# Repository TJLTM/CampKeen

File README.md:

# CampKeen
An OpenSource RV monitoring hardware project. Currently i'm targeting my setup but leaving enough to adapt to other systems. This will allow a central place to monitor all of the various things in an RV and will be able to be integrated with an external system like Home assistant (when I get to that it will have a separate Repo for the component) or custom setups. As well control some things around the RV. Like in this case, i have small holding tanks and to keep them from overflowing i have added water pump and city (external water hook up control) in both the bathroom and in the kitchen. This does not have a wifi or Ethernet capability. This is RS232 or USB (via the MEGA2560) device only. 

What this can monitor: 
1. Holding Tanks - Grey/Sewage via galvanic sensors (posts in the tank) these are the ones i'm using (https://www.amazon.com/gp/product/B07YVK2V2K/ref=ppx_yo_dt_b_search_asin_title?ie=UTF8&psc=1 and https://www.amazon.com/gp/product/B07SVDTHHG/ref=ppx_yo_dt_b_search_asin_title?ie=UTF8&psc=1)
2. Fresh water tank - Resistance (https://www.amazon.com/gp/product/B00Y831WPM/ref=ppx_yo_dt_b_asin_title_o07_s01?ie=UTF8&th=1&psc=1)
3. Camper Battery Voltage
4. Power/Energy Monitoring (https://github.com/CircuitSetup/Split-Single-Phase-Energy-Meter)
5. Tempetures around the RV especially and Fridge and Freezer (https://www.amazon.com/gp/product/B087NMHGX8/ref=ppx_yo_dt_b_asin_title_o07_s01?ie=UTF8&psc=1)
6. Generator Fuel Pressure (https://www.amazon.com/gp/product/B07N8SX347/ref=ppx_yo_dt_b_search_asin_title?ie=UTF8&th=1 be careful of these they may or may not be DOA or last only a few weeks depending i haven't found a good source that isn't a crap shoot) 
7. LPG tank level - No link as this is the original tank and sensor that came with the 1978 Pace Arrow it's resistance based but single wire it is similar to https://parts.unitedrv.com/products/remote-ohm-sender-lp-gas-tank-90-degree?currency=USD&variant=36385562881&_vsrefdom=adwords&msclkid=ae7c158e8c431c0739b97415690580d9&utm_source=bing&utm_medium=cpc&utm_campaign=**LP%20Shopping%20-%20Catch%20All&utm_term=4583245501779595&utm_content=Catch%20All

What this can control:
1. WaterPump
2. City Water Valve (https://www.amazon.com/gp/product/B07N6246YB/ref=ppx_yo_dt_b_asin_title_o05_s00?ie=UTF8&th=1)
I do this with push buttons (two one in the kitchen and one in the bathroom for my set up) with LEDs to let you know that the water is on. Be it the City Water or Tank Via the pump. 
i have also included a timer. that can be set for how long you would ike the water to remain on when either button is pressed.

Other Stuff
1. There are 6 spare outputs that can be used to control whatever you want 
2. Same goes for 6 spare inputs 
3. I2C output for an 20x4 LCD to display current status (https://www.amazon.com/gp/product/B07MTFDHXZ/ref=ppx_yo_dt_b_search_asin_title?ie=UTF8&psc=1)
4. Siren to alert when the tanks are full
5. Warning LED (This and the siren can be programmed for other items for warnings) 
6. 2 Spare Buffered ADCs with POTs 

Some Specs and Installation Notes: 
1. I designed this for 12Vdc systems only so i'm not sure if it would work on a 24Vdc system might. might not. 
2. The Inputs are buffered and you can just supply 12Vdc in as a logical 'On' 
3. Outputs, Although technically you could power the waterpump directly off of the unit. this is not recommended. nor encouraged in any way, shape or form. These outputs are used to trigger remove 12Vdc relays like the following: https://www.summitracing.com/parts/pco-5591pt

currently working on https://github.com/TJLTM/CampKeen-HomeAssistant-Custom-Integration this may roll into a true python package later on to handle communication 

FUTURE: 
Better docs with installation pictures for my setup.

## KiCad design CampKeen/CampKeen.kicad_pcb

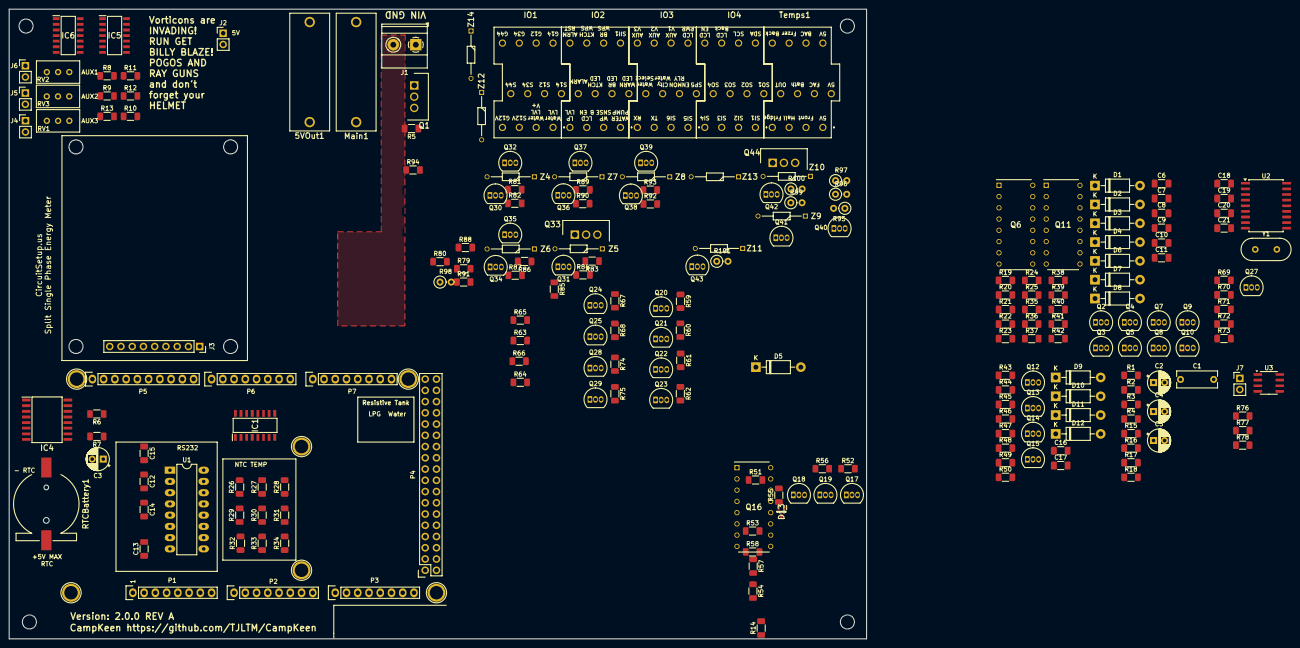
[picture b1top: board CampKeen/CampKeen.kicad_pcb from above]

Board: 4 copper layers, 193.7 x 142.2 mm, 228 parts (0 on the bottom side), 176 nets, no tracks yet.

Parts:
5VOut1: VS; BK_HTC-15M
C1: 0.1uF; C_Rect_L9.0mm_W3.6mm_P7.50mm_MKT
C2, C3, C4, C5: 1uF; CP_Radial_D5.0mm_P2.50mm
C6, C7, C8, C9, C10, C11, C12, C13, C14, C15, C16, C17: 22nF; C_1206_3216Metric_Pad1.33x1.80mm_HandSolder
C18, C19: 22pf; C_1206_3216Metric_Pad1.33x1.80mm_HandSolder
C20, C21: 100nf; C_1206_3216Metric_Pad1.33x1.80mm_HandSolder
D1, D2, D3, D4, D5, D6, D7, D8, D9, D10, D11, D12: 1N4007; D_DO-41_SOD81_P10.16mm_Horizontal
D13: PESD5V0L2UU,115; SOT65P210X110-3N
IC1: CD74HC4050ME4; SOIC127P600X175-16N
IC4: DS3231SN#; SOIC127P1032X265-16N
IC5, IC6: SN7404DR; SOIC127P600X175-14N
IO1: IO1; 1727751
IO2: IO2; 1727751
IO3: IO3; 1727751
IO4: IO4; 1727751
J1: Vin; TerminalBlock_Phoenix_MKDS-1,5-2-5.08_1x02_P5.08mm_Horizont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
J2, J4, J5, J6, J7: Conn_01x02; PinHeader_1x02_P2.54mm_Vertical
J3: CircuitSetupsSplitPhase; PinSocket_1x09_P2.54mm_Vertical
Main1: VS; BK_HTC-15M
P1: Power; Socket_Strip_Arduino_1x08
P2, P3: Analog; Socket_Strip_Arduino_1x08
P4: Digital; Socket_Strip_Arduino_2x18
P5: PWM; Socket_Strip_Arduino_1x10
P6: PWM; Socket_Strip_Arduino_1x08
P7: Communication; Socket_Strip_Arduino_1x08
P8, P9, P10, P11, P12, P13: CONN_01X01; Arduino_1pin
Q1, Q33, Q44: IRF9Z34NPBF; TO254P469X1042X1967-3P
Q2, Q3, Q4, Q5, Q7, Q8, Q9, Q10, Q12, Q13, Q14, Q15, Q17, Q18, Q19, Q20, Q21, Q22, Q23, Q24, Q25, Q27, Q28, Q29, Q30, Q31, Q32, Q34, Q35, Q36, Q37, Q38, Q39, Q40, Q41, Q42, Q43: 2N7000; TO-92_Inline
Q6, Q11, Q16: LTV-847; DIP762W60P254L1984H450Q16N
R1, R57, R59, R63, R65, R68, R71, R74, R78, R80, R83, R86, R89, R92: 100k; R_1206_3216Metric_Pad1.30x1.75mm_HandSolder
R2, R3, R10, R11, R12, R13, R14, R15, R16, R17, R18, R58, R60, R64, R66, R69, R72, R75, R79, R81, R84, R87, R90, R93, R94: 10k; R_1206_3216Metric_Pad1.30x1.75mm_HandSolder
R4, R6, R7, R8, R9: 47K; R_1206_3216Metric_Pad1.30x1.75mm_HandSolder
R5: 19.2K; R_1206_3216Metric_Pad1.30x1.75mm_HandSolder
R19, R20, R21, R22, R27, R28, R30, R32, R43, R44, R45, R46, R55, R56, R61, R62, R67, R70, R73, R76, R77, R82, R85, R88, R91: 1M; R_1206_3216Metric_Pad1.30x1.75mm_HandSolder
R23, R25, R26, R35, R37, R38, R47, R48, R49, R50: 330; R_1206_3216Metric_Pad1.30x1.75mm_HandSolder
R24, R36: 300; R_1206_3216Metric_Pad1.30x1.75mm_HandSolder
R29, R31, R33, R34, R39, R40, R41, R42, R51, R52, R53, R54: 22k; R_1206_3216Metric_Pad1.30x1.75mm_HandSolder
R95: 17k; R_Axial_DIN0207_L6.3mm_D2.5mm_P2.54mm_Vertical
R96: 120; R_Axial_DIN0207_L6.3mm_D2.5mm_P2.54mm_Vertical
R97: 1M; R_Axial_DIN0207_L6.3mm_D2.5mm_P2.54mm_Vertical
R98: 100k; R_Axial_DIN0207_L6.3mm_D2.5mm_P2.54mm_Vertical
R99: 10k; R_Axial_DIN0207_L6.3mm_D2.5mm_P2.54mm_Vertical
R100, R101: 47; R_Axial_DIN0207_L6.3mm_D2.5mm_P2.54mm_Vertical
RTCBattery1: S8411-45R; S8411-45R_1
RV1, RV2, RV3: 500k; Potentiometer_Bourns_3296W_Vertical
Temps1: Temps; 1727751
U1: MAX232; DIP-16_W7.62mm_LongPads
U2: MCP2515-xSO; SOIC-18W_7.5x11.6mm_P1.27mm
U3: MCP2551-I-SN; SOIC-8_3.9x4.9mm_P1.27mm
Y1: 16MHz; Crystal_HC49-U_Vertical
Z4, Z5, Z6, Z7, Z8, Z9, Z10, Z11, Z12, Z13, Z14: BZX79C10; DIOAD1068W53L380D172

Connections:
+3V3: IC1.1 (VCC), P1.4
+5P: C1.1, IC4.2 (VCC), P1.5, P4.35, P4.36
+5V: 5VOut1.2, C5.2, C20.1, C21.1, IC5.14 (VCC), IC6.14 (VCC), J2.1, R2.1, R3.1, R23.1, R24.1, R25.1, R26.1, R29.1, R31.1, R33.1, R34.1, R35.1, R36.1, R37.1, R38.1, R39.1, R40.1, R41.1, R42.1, R47.1, R48.1, R49.1, R50.1, R51.1, R52.1, R53.1, R54.1, R94.2, Temps1.1, Temps1.2, Temps1.3, U1.16 (VCC), U2.18 (VDD), U3.3 (VDD)
+12V: Q1.3, Q33.3, R4.2, R57.1, R59.1, R63.1, R65.1, R68.1, R71.1, R74.1, R78.1, R80.1, R83.1, R86.1, R89.1, R92.1, Z4.1, Z5.1, Z6.1, Z7.1, Z8.1, Z9.1, Z10.1, Z11.1, Z12.1, Z13.1
+BATT: J1.1, Main1.1
/3.3CS: IC1.15 (6Y), J3.6
/3.3MISO: IC1.5 (2A), J3.4
/3.3MOSI: IC1.6 (3Y), J3.3
/3.3SCLK: IC1.2 (1Y), J3.5
/CANBUS-MCP2515/RXtoCANTC: U2.2 (RXCAN), U3.4 (RXD)
/CANBUS-MCP2515/TXtoCANTC: U2.1 (TXCAN), U3.1 (TXD)
/Inputs with interrupts/AlarmResetTTL: IC5.1 (1A), Q16.16 (COLLECTOR_4), R51.2
/Inputs with interrupts/BathroomTTL: IC5.5 (3A), Q16.12 (COLLECTOR_2), R53.2
/Inputs with interrupts/KitchenTTL: IC5.3 (2A), Q16.10 (COLLECTOR_1), R54.2
/Inputs with interrupts/ShowerInTTL: IC5.13 (6A), Q16.14 (COLLECTOR_3), R52.2
/Inputs/EnableLCDIn: C7.1, Q3.2 (G), R20.1
/Inputs/EnableLCDTTL: Q6.14 (COLLECTOR_3), R33.2
/Inputs/LCDBackLIGHTIn: C8.1, Q4.2 (G), R21.1
/Inputs/LCDBackLIGHTTTL: Q6.12 (COLLECTOR_2), R31.2
/Inputs/SP1TTL: IC6.5 (3A), Q11.16 (COLLECTOR_4), R42.2
/Inputs/SP2TTL: IC6.13 (6A), Q11.14 (COLLECTOR_3), R41.2
/Inputs/SP3TTL: IC6.11 (5A), Q11.12 (COLLECTOR_2), R40.2
/Inputs/SP4TTL: IC6.9 (4A), Q11.10 (COLLECTOR_1), R39.2
/Inputs/WaterPumpSenseTTL: IC5.11 (5A), Q6.16 (COLLECTOR_4), R34.2
/Inputs/WaterSourceTTL: IC6.3 (2A), Q6.10 (COLLECTOR_1), R29.2
A0: P2.1, R6.2
A1: IO2.10, P2.2, R100.1
A2: IO1.1, P2.3, R101.2
A3: P2.4, R11.2, Temps1.5
A4: P2.5, R12.2, Temps1.6
A5: P2.6, R18.2, Temps1.7
A6: P2.7, R17.2, Temps1.8
A7: P2.8, R16.2, Temps1.9
A8: P3.1, R15.2, Temps1.10
A9: P3.2, R14.2, Temps1.11
A10: P3.3, R13.2, Temps1.12
A11: P3.4, R10.2, Temps1.4
A12: P3.5, R8.2
A13: P3.6, R9.2
A14: IC4.14 (VBAT), P3.7, RTCBattery1.1 (+)
A15: P3.8, R7.2
AUXVoltage0: IO3.6, RV2.1
AUXVoltage1: IO3.9, RV3.1
AUXVoltage2: IO3.12, RV1.1
AlarmTTL: IC5.2 (1Y), P6.5
BRLED: P6.1, Q18.2 (G), R56.1
BathRoomTTL: IC5.6 (3Y), P4.16
CAN1CS: P4.30, U2.16 (~CS)
CLK: IC1.3 (1A), P4.3, U2.13 (SCK)
COMRX5to33TTL: IC1.12 (5Y), P7.6
COMRXTTL: P7.4, U1.12 (R1OUT)
COMTX5to33TTL: IC1.9 (4A), P7.5
COMTXTTL: P7.3, U1.11 (T1IN)
CWV: P4.27, Q29.2 (G), Q40.2 (G), R73.1
EnCS: IC1.14 (6A), P4.31
GND: C1.2, C3.1, C6.2, C7.2, C8.2, C9.2, C10.2, C11.2, C12.2, C13.2, C14.2, C15.2, C16.2, C17.2, C18.2, C19.2, C20.2, C21.2, D13.3 (COMMON_ANODE), IC1.8 (GND), IC4.5 (N.C._1), IC4.6 (N.C._2), IC4.7 (N.C._3), IC4.8 (N.C._4), IC4.9 (N.C._5), IC4.10 (N.C._6), IC4.11 (N.C._7), IC4.12 (N.C._8), IC4.13 (GND), IC5.7 (GND), IC6.7 (GND), J1.2, J2.2, J3.1, P1.6, P1.7, P4.1, P4.2, P5.4, Q2.1 (S), Q3.1 (S), Q4.1 (S), Q5.1 (S), Q6.9 (EMITTER_1), Q6.11 (EMITTER_2), Q6.13 (EMITTER_3), Q6.15 (EMITTER_4), Q7.1 (S), Q8.1 (S), Q9.1 (S), Q10.1 (S), Q11.9 (EMITTER_1), Q11.11 (EMITTER_2), Q11.13 (EMITTER_3), Q11.15 (EMITTER_4), Q12.1 (S), Q13.1 (S), Q14.1 (S), Q15.1 (S), Q16.9 (EMITTER_1), Q16.11 (EMITTER_2), Q16.13 (EMITTER_3), Q16.15 (EMITTER_4), Q17.1 (S), Q18.1 (S), Q19.1 (S), Q20.1 (S), Q21.1 (S), Q22.1 (S), Q23.1 (S), Q24.1 (S), Q25.1 (S), Q27.1 (S), Q28.1 (S), Q29.1 (S), Q30.1 (S), Q31.1 (S), Q32.1 (S), Q34.1 (S), Q35.1 (S), Q36.1 (S), Q37.1 (S), Q38.1 (S), Q39.1 (S), Q40.1 (S), Q41.1 (S), Q42.1 (S), Q43.1 (S), R1.2, R5.1, R6.1, R7.1, R8.1, R9.1, R10.1, R11.1, R12.1, R13.1, R14.1, R15.1, R16.1, R17.1, R18.1, R19.2, R20.2, R21.2, R22.2, R27.2, R28.2, R30.2, R32.2, R43.2, R44.2, R45.2, R46.2, R55.2, R56.2, R61.2, R62.2, R67.2, R70.2, R73.2, R76.2, R77.2, R82.2, R85.2, R88.2, R91.2, R95.2, R97.2, R101.1, RTCBattery1.2 (-), RV1.3, RV2.3, RV3.3, U1.15 (GND), U2.9 (VSS), U3.2 (VSS)
IO14: IO1.4, Q44.2, R100.2
IO23: C15.1, IO2.3, Q13.2 (G), R44.1
IO24: C6.1, IO2.4, Q2.2 (G), Q20.2 (G), R19.1
IO26: C16.1, IO2.6, Q14.2 (G), Q19.2 (G), R45.1
IO29: C17.1, IO2.9, Q15.2 (G), R46.1
IO41: C10.1, D13.1 (CATHODE_1), IO4.1, J7.1, Q7.2 (G), Q24.2 (G), R27.1, U3.7 (CANH)
IO42: IO4.2, Q33.2
IO44: C11.1, D13.2 (CATHODE_2), IO4.4, Q8.2 (G), Q28.2 (G), R28.1, R96.2, U3.6 (CANL)
IO47: C12.1, IO4.7, Q9.2 (G), R30.1
IO212: C14.1, IO2.12, Q12.2 (G), R43.1
IO311: C9.1, IO3.11, Q5.2 (G), Q23.2 (G), R22.1
IO410: C13.1, IO4.10, Q10.2 (G), R32.1
KLED: P6.2, Q21.2 (G), Q34.2 (G), R61.1
KitchenTTL: IC5.4 (2Y), P4.18
MISO: IC1.4 (2Y), P4.5, U2.15 (SO)
MOSI: IC1.7 (3A), P4.6, U2.14 (SI)
unnamed: D1.2 (A), Q6.2 (CATHODE_1)
unnamed: D1.1 (K), Q2.3 (D)
unnamed: D2.2 (A), Q6.4 (CATHODE_2)
unnamed: D2.1 (K), Q3.3 (D)
unnamed: D3.2 (A), Q6.6 (CATHODE_3)
unnamed: D3.1 (K), Q4.3 (D)
unnamed: D4.2 (A), Q6.8 (CATHODE_4)
unnamed: D4.1 (K), Q5.3 (D)
unnamed: D5.2 (A), Q11.2 (CATHODE_1)
unnamed: D5.1 (K), Q7.3 (D), Q20.3 (D)
unnamed: D6.2 (A), Q11.4 (CATHODE_2)
unnamed: D6.1 (K), Q8.3 (D)
unnamed: D7.2 (A), Q11.6 (CATHODE_3)
unnamed: D7.1 (K), Q9.3 (D)
unnamed: D8.2 (A), Q11.8 (CATHODE_4)
unnamed: D8.1 (K), Q10.3 (D)
unnamed: D9.2 (A), Q16.2 (CATHODE_1)
unnamed: D9.1 (K), Q12.3 (D)
unnamed: D10.2 (A), Q16.4 (CATHODE_2)
unnamed: D10.1 (K), Q13.3 (D)
unnamed: D11.2 (A), Q16.6 (CATHODE_3)
unnamed: D11.1 (K), Q14.3 (D)
unnamed: D12.2 (A), Q16.8 (CATHODE_4)
unnamed: D12.1 (K), Q15.3 (D)
unnamed: R4.1, R5.2
unnamed: J4.2, RV1.2
unnamed: J5.2, RV2.2
unnamed: J6.2, RV3.2
unnamed: J7.2, R96.1
unnamed: Q44.3, R98.1, Z14.1
unnamed: Main1.2, Q1.2
unnamed: Q1.1, R1.1
unnamed: Q6.1 (ANODE_1), R26.2
unnamed: Q6.3 (ANODE_2), R25.2
unnamed: Q6.5 (ANODE_3), R24.2
unnamed: Q6.7 (ANODE_4), R23.2
unnamed: Q11.1 (ANODE_1), R38.2
unnamed: Q11.3 (ANODE_2), R37.2
unnamed: Q11.5 (ANODE_3), R36.2
unnamed: Q11.7 (ANODE_4), R35.2
unnamed: Q16.1 (ANODE_1), R50.2
unnamed: Q16.3 (ANODE_2), R49.2
unnamed: Q16.5 (ANODE_3), R48.2
unnamed: Q16.7 (ANODE_4), R47.2
unnamed: Q17.3 (D), R58.2
unnamed: Q18.3 (D), R60.2
unnamed: R57.2, R58.1
unnamed: R59.2, R60.1
unnamed: Q21.3 (D), R64.2
unnamed: Q22.3 (D), R66.2
unnamed: R63.2, R64.1
unnamed: R65.2, R66.1, Z4.2
unnamed: Q25.3 (D), R69.2
unnamed: R68.2, R69.1, Z5.2
unnamed: Q27.3 (D), R72.2
unnamed: R71.2, R72.1, Z6.2
unnamed: Q29.3 (D), R75.2
unnamed: R74.2, R75.1, Z7.2
unnamed: Q31.3 (D), R79.2
unnamed: Q32.3 (D), R81.2
unnamed: Q33.1, R78.2, R79.1, Z8.2
unnamed: R80.2, R81.1, Z9.2
unnamed: Q35.3 (D), R84.2
unnamed: R83.2, R84.1, Z10.2
unnamed: Q37.3 (D), R87.2
unnamed: R86.2, R87.1, Z11.2
unnamed: Q39.3 (D), R90.2
unnamed: R89.2, R90.1, Z12.2
unnamed: Q41.3 (D), R93.2
unnamed: R92.2, R93.1, Z13.2
unnamed: Q43.3 (D), R99.2
unnamed: Q44.1, R98.2, R99.1, Z14.2
unnamed: C2.1, U1.1 (C1+)
unnamed: C2.2, U1.3 (C1-)
unnamed: C4.1, U1.4 (C2+)
unnamed: C4.2, U1.5 (C2-)
unnamed: C5.1, U1.2 (VS+)
unnamed: C3.2, U1.6 (VS-)
unnamed: C19.1, U2.8 (OSC1), Y1.1
unnamed: C18.1, U2.7 (OSC2), Y1.2
unnamed: R94.1, U2.17 (~RESET)
unnamed: R95.1, U3.8 (Rs)
RTankPOWER: P4.33, Q43.2 (G), R97.1
RX232: IO3.10, U1.13 (R1IN)
SCL: IC4.16 (SCL), IO4.6, P7.8, R2.2
SDA: IC4.15 (SDA), IO4.3, P7.7, R3.2
SHOWERLED: P5.10, Q22.2 (G), R62.1
SO1: P4.7, Q31.2 (G), Q42.2 (G), R76.1
SO2: P4.9, Q35.2 (G), R82.1
SO3: P4.11, Q37.2 (G), R85.1
SO4: P4.13, Q39.2 (G), R88.1
SO5: P4.15, Q41.2 (G), R91.1
SO6: P4.17, Q32.2 (G), R77.1
SPIn1: IC6.6 (3Y), P4.22
SPIn2: IC6.12 (6Y), P4.24
SPIn3: IC6.10 (5Y), P4.26
SPIn4: IC6.8 (4Y), P4.28
ShowerTTL: IC5.12 (6Y), P4.12
TX232: IO3.7, U1.14 (T1OUT)
WLED: P6.3, Q25.2 (G), Q36.2 (G), R67.1
WP: P4.29, Q27.2 (G), Q38.2 (G), R70.1
WPS: IC5.10 (5Y), P4.14
WSS: IC6.4 (2Y), P4.20
WSiren: P6.4, Q17.2 (G), Q30.2 (G), R55.1

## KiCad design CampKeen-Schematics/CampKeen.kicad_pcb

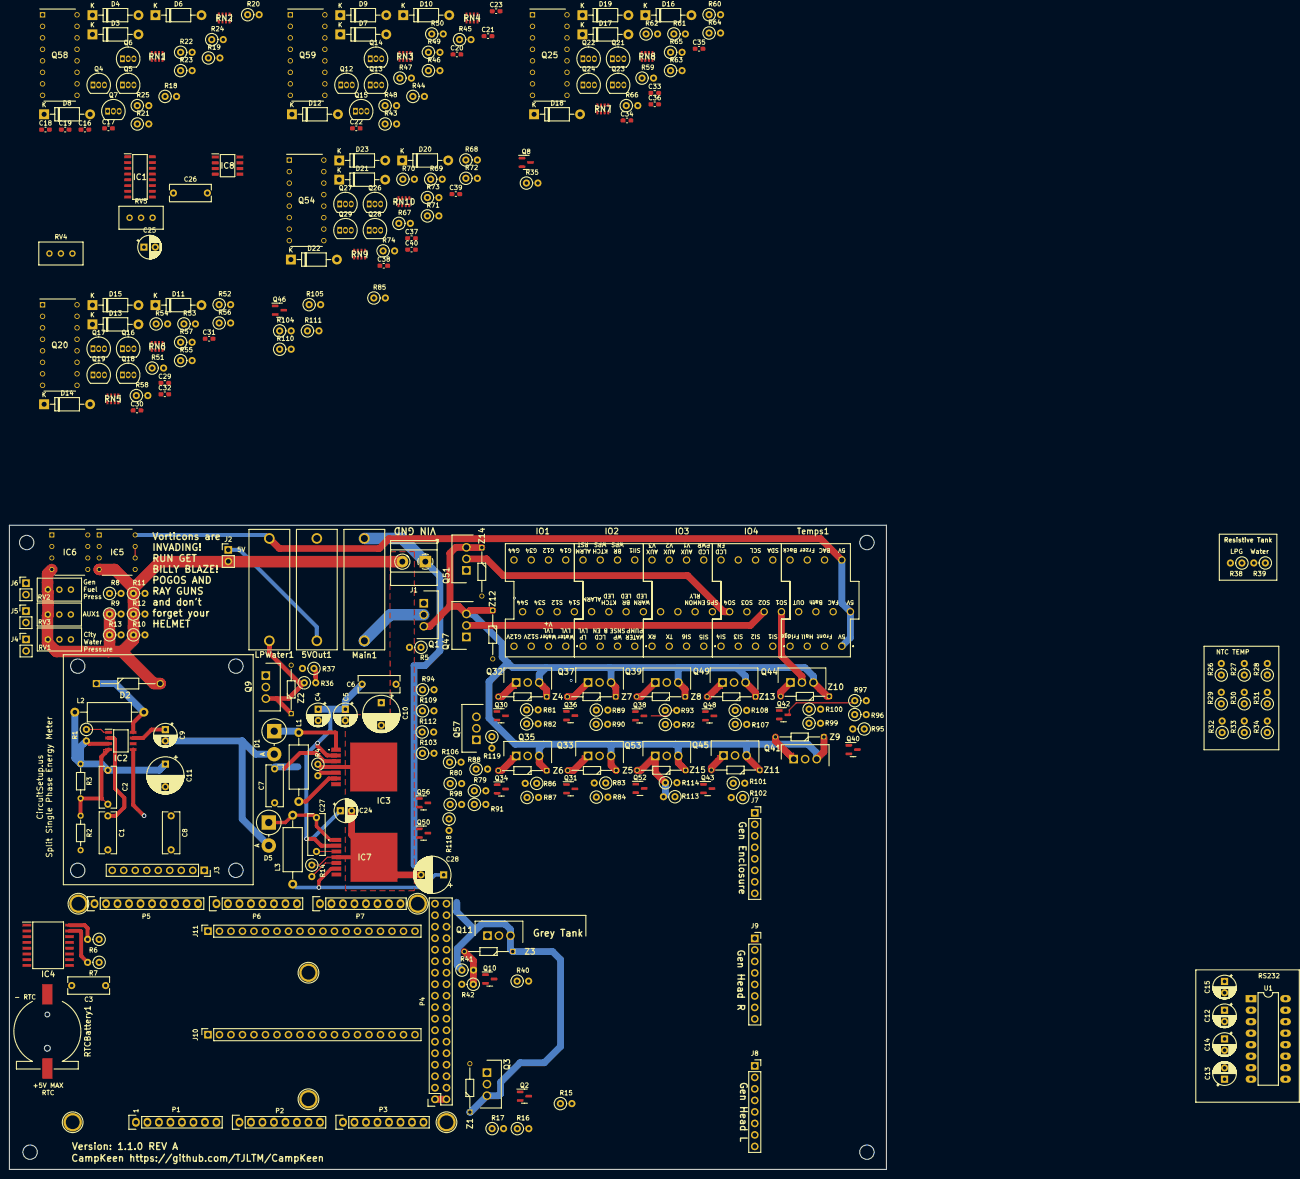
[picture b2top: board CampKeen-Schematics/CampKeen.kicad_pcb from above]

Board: 4 copper layers, 193.7 x 142.2 mm, 308 parts (0 on the bottom side), 238 nets.

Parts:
5VOut1: VS; BK_HTC-15M
C1, C3, C8: 0.1uF; C_Rect_L9.0mm_W3.6mm_P7.50mm_MKT
C2: 3.3nF; C_Rect_L9.0mm_W3.6mm_P7.50mm_MKT
C4, C5, C24, C25: 15uF; CP_Radial_D5.0mm_P2.50mm
C6, C26: 0.47uF; C_Rect_L9.0mm_W3.6mm_P7.50mm_MKT
C7, C27: 0.01uF; C_Rect_L9.0mm_W3.6mm_P7.50mm_MKT
C9: 68uF; CP_Radial_D5.0mm_P2.50mm
C10, C11: 120uF; CP_Radial_D8.0mm_P5.00mm
C12, C13, C14, C15: 1uF; CP_Radial_D5.0mm_P2.50mm
C16, C17, C18, C19, C20, C21, C22, C23, C29, C30, C31, C32, C33, C34, C35, C36, C37, C38, C39, C40: 22nF; C_0603_1608Metric_Pad1.08x0.95mm_HandSolder
C28: 180uF; CP_Radial_D8.0mm_P5.00mm
D1, D5: SR305-TP; D_DO-201AD_P5.08mm_Vertical_AnodeUp
D2: 1N5817; DIOAD1414W86L464D238
D3, D4, D6, D7, D8, D9, D10, D11, D12, D13, D14, D15, D16, D17, D18, D19, D20, D21, D22, D23: 1N4007; D_DO-41_SOD81_P10.16mm_Horizontal
IC1: CD74HC4050ME4; SOIC127P600X175-16N
IC2: LM2597MX-ADJ_NOPB; SOIC127P600X175-8N
IC3: LM2670SX-5.0_NOPB; LM2670SX50NOPB
IC4: DS3231SN#; SOIC127P1032X265-16N
IC5, IC6: OPA2340PA; DIP794W53P254L959H508Q8N
IC7: LM2670SX-3.3_NOPB; LM2670SX33NOPB
IC8: P82B715TD,112; SOIC127P600X175-8N
IO1: IO1; 1727751
IO2: IO2; 1727751
IO3: IO3; 1727751
IO4: IO4; 1727751
J1: Vin; TerminalBlock_Phoenix_MKDS-1,5-2-5.08_1x02_P5.08mm_Horizont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
J2, J4, J5, J6: Conn_01x02; PinHeader_1x02_P2.54mm_Vertical
J3: CircuitSetupsSplitPhase; PinSocket_1x09_P2.54mm_Vertical
J7: GenEnclosure; PinSocket_1x08_P2.54mm_Vertical
J8: GenHeadL; PinSocket_1x08_P2.54mm_Vertical
J9: GenHeadR; PinSocket_1x08_P2.54mm_Vertical
J10, J11: Conn_01x19; PinSocket_1x19_P2.54mm_Vertical
L1: 33uH; L_Axial_L9.5mm_D4.0mm_P15.24mm_Horizontal_Fastron_SMCC
L2: 150mH; L_Axial_L9.5mm_D4.0mm_P15.24mm_Horizontal_Fastron_SMCC
L3: 22uH; L_Axial_L9.5mm_D4.0mm_P15.24mm_Horizontal_Fastron_SMCC
LPWater1: LPGVS; BK_HTC-15M
Main1: VS; BK_HTC-15M
P1: Power; Socket_Strip_Arduino_1x08
P2, P3: Analog; Socket_Strip_Arduino_1x08
P4: Digital; Socket_Strip_Arduino_2x18
P5: PWM; Socket_Strip_Arduino_1x10
P6: PWM; Socket_Strip_Arduino_1x08
P7: Communication; Socket_Strip_Arduino_1x08
P8, P9, P10, P11, P12, P13: CONN_01X01; Arduino_1pin
Q1, Q3, Q9, Q11, Q32, Q33, Q35, Q37, Q39, Q41, Q44, Q45, Q47, Q49, Q51, Q53, Q57: IRF9Z34NPBF; TO254P469X1042X1967-3P
Q2, Q8, Q10, Q30, Q31, Q34, Q36, Q38, Q40, Q42, Q43, Q46, Q48, Q50, Q52, Q56: 2N7002; SOT-23
Q4, Q5, Q6, Q7, Q12, Q13, Q14, Q15, Q16, Q17, Q18, Q19, Q21, Q22, Q23, Q24, Q26, Q27, Q28, Q29: 2N7000; TO-92_Inline
Q20, Q25, Q54, Q58, Q59: LTV-847; DIP762W60P254L1984H450Q16N
R1: 4.7k; R_Axial_DIN0207_L6.3mm_D2.5mm_P2.54mm_Vertical
R2: 1k; R_Axial_DIN0204_L3.6mm_D1.6mm_P7.62mm_Horizontal
R3: 6.2k; R_Axial_DIN0204_L3.6mm_D1.6mm_P7.62mm_Horizontal
R4, R14: 1k; R_Axial_DIN0207_L6.3mm_D2.5mm_P2.54mm_Vertical
R5, R16, R36, R41, R81, R83, R86, R89, R92, R95, R99, R101, R104, R107, R110, R113, R119: 100k; R_Axial_DIN0207_L6.3mm_D2.5mm_P2.54mm_Vertical
R6, R7, R17, R26, R27, R28, R29, R30, R31, R32, R33, R34, R37, R42, R82, R84, R87, R90, R93, R96, R100, R102, R105, R108, R111, R114: 10k; R_Axial_DIN0207_L6.3mm_D2.5mm_P2.54mm_Vertical
R8, R10, R11, R12, R13: 47K; R_Axial_DIN0207_L6.3mm_D2.5mm_P2.54mm_Vertical
R9: 19.2K; R_Axial_DIN0207_L6.3mm_D2.5mm_P2.54mm_Vertical
R15, R35, R40, R79, R80, R85, R88, R91, R94, R97, R98, R103, R106, R109, R112, R118: 1M; R_Axial_DIN0207_L6.3mm_D2.5mm_P2.54mm_Vertical
R18, R19, R20, R21, R43, R44, R45, R46, R51, R52, R53, R54, R59, R60, R61, R62, R67, R68, R69, R70: 470; R_Axial_DIN0207_L6.3mm_D2.5mm_P2.54mm_Vertical
R22, R23, R24, R25, R47, R48, R49, R50, R55, R56, R57, R58, R63, R64, R65, R66, R71, R72, R73, R74: 5K; R_Axial_DIN0207_L6.3mm_D2.5mm_P2.54mm_Vertical
R38, R39: 47; R_Axial_DIN0207_L6.3mm_D2.5mm_P2.54mm_Vertical
RN1, RN3, RN5, RN7, RN9: EXB-38V331JV; EXB38V472JV
RN2, RN4, RN6, RN8, RN10: EXB-38V223JV; EXB38V472JV
RTCBattery1: S8411-45R; S8411-45R_1
RV1, RV2, RV3, RV4, RV5: 500k; Potentiometer_Bourns_3296W_Vertical
Temps1: Temps; 1727751
U1: MAX232; DIP-16_W7.62mm_LongPads
Z1, Z2, Z3, Z4, Z5, Z6, Z7, Z8, Z9, Z10, Z11, Z12, Z13, Z14, Z15: BZX79C10; DIOAD1068W53L380D172

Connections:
+3V3: C28.1, IC1.1 (VCC), IC7.6 (FEEDBACK/FB), J10.1, L3.2, P1.4
+5P: C3.1, IC4.2 (VCC), P1.5, P4.35, P4.36
+5V: 5VOut1.2, C15.2, IC5.8 (V+), IC6.8 (V+), IC8.8 (VCC), J2.1, J7.1, J8.1, J9.1, LPWater1.2, R6.1, R7.1, RN1.5, RN1.6, RN1.7, RN1.8, RN2.5, RN2.6, RN2.7, RN2.8, RN3.5, RN3.6, RN3.7, RN3.8, RN4.5, RN4.6, RN4.7, RN4.8, RN5.5, RN5.6, RN5.7, RN5.8, RN6.5, RN6.6, RN6.7, RN6.8, RN7.5, RN7.6, RN7.7, RN7.8, RN8.5, RN8.6, RN8.7, RN8.8, RN9.5, RN9.6, RN9.7, RN9.8, RN10.5, RN10.6, RN10.7, RN10.8, RV4.1, RV5.1, Temps1.1, Temps1.2, Temps1.3, U1.16 (VCC)
+9V: C2.2, C11.1, IC2.3 (BIAS_SUPPLY), L2.2, P1.8, R1.2, R3.1
+12V: C4.1, C5.1, C6.1, C9.1, C24.1, C25.1, C26.1, IC2.7 (+VIN), IC3.2 (INPUT), IC7.2 (INPUT), Q1.3, Q32.3, Q33.3, Q35.3, Q37.3, Q39.3, Q41.3, Q44.3, Q45.3, Q47.3, Q49.3, Q51.3, Q53.3, Q57.3, R8.2, R81.1, R83.1, R86.1, R89.1, R92.1, R95.1, R99.1, R101.1, R104.1, R107.1, R110.1, R113.1, R119.1, Z4.1, Z5.1, Z6.1, Z7.1, Z8.1, Z9.1, Z10.1, Z11.1, Z12.1, Z13.1, Z14.1, Z15.1
+BATT: J1.1, Main1.1, Q3.3, Q11.3, R16.1, R41.1, Z1.1, Z3.1
/3.3CS: IC1.15 (6Y), J3.6
/3.3MISO: IC1.5 (2A), J3.4
/3.3MOSI: IC1.6 (3Y), J3.3
/3.3SCLK: IC1.2 (1Y), J3.5
A0: IC5.1 (OUTA), IC5.2 (-INA), P2.1, R10.2
A1: IO2.10, P2.2, R38.1
A2: IO1.1, P2.3, R39.2
A3: P2.4, R27.2, Temps1.5
A4: P2.5, R28.2, Temps1.6
A5: P2.6, R34.2, Temps1.7
A6: P2.7, R33.2, Temps1.8
A7: P2.8, R32.2, Temps1.9
A8: P3.1, R31.2, Temps1.10
A9: P3.2, R30.2, Temps1.11
A10: P3.3, R29.2, Temps1.12
A11: P3.4, R26.2, Temps1.4
A12: IC5.6 (-INB), IC5.7 (OUTB), P3.5, R12.2
A13: IC6.6 (-INB), IC6.7 (OUTB), P3.6, R13.2
A14: IC4.14 (VBAT), P3.7, RTCBattery1.1 (+)
A15: IC6.1 (OUTA), IC6.2 (-INA), P3.8, R11.2
AUXVoltage1: IO3.9, RV3.1
AlarmTTL: P6.5, Q20.16 (COLLECTOR_4), RN6.1
BRLED: P6.1, Q31.2 (G), R80.1
BathRoomTTL: P7.6, Q20.12 (COLLECTOR_2), RN6.3
CLK: IC1.3 (1A), J7.4, J8.4, J9.4, P4.3
COMRXTTL: P7.4, U1.12 (R1OUT)
COMTXTTL: P7.3, U1.11 (T1IN)
CWV: P4.27, Q40.2 (G), R94.1
CityWaterPressure: IO3.12, RV1.1
ENLCD: P4.16, Q25.14 (COLLECTOR_3), RN8.2
ESPCOMTXTTL5V: IC1.9 (4A), P7.1
EnCS: IC1.14 (6A), P4.31
EspRX: IC1.10 (4Y), J11.5
G1-2: P4.17, Q59.14 (COLLECTOR_3), RN4.2
G1-4: P4.15, Q59.16 (COLLECTOR_4), RN4.1
G3-4: P4.19, Q59.12 (COLLECTOR_2), RN4.3
G4-4: P4.21, Q59.10 (COLLECTOR_1), RN4.4
GND: C1.2, C3.2, C4.2, C5.2, C6.2, C8.2, C9.2, C10.2, C11.2, C13.1, C16.2, C17.2, C18.2, C19.2, C20.2, C21.2, C22.2, C23.2, C24.2, C25.2, C26.2, C28.2, C29.2, C30.2, C31.2, C32.2, C33.2, C34.2, C35.2, C36.2, C37.2, C38.2, C39.2, C40.2, D1.2 (A), D2.2, D5.2 (A), IC1.8 (GND), IC2.6 (GROUND), IC3.4 (GND), IC3.8 (EP), IC4.5 (N.C._1), IC4.6 (N.C._2), IC4.7 (N.C._3), IC4.8 (N.C._4), IC4.9 (N.C._5), IC4.10 (N.C._6), IC4.11 (N.C._7), IC4.12 (N.C._8), IC4.13 (GND), IC5.4 (V-), IC6.4 (V-), IC7.4 (GND), IC7.8 (EP), IC8.1 (N.C._1), IC8.4 (GND), IC8.5 (N.C._2), J1.2, J2.2, J3.1, J7.2, J8.2, J9.2, J10.14, J11.1, J11.7, P1.6, P1.7, P4.1, P4.2, P5.4, Q2.1 (S), Q4.1 (S), Q5.1 (S), Q6.1 (S), Q7.1 (S), Q8.1 (S), Q10.1 (S), Q12.1 (S), Q13.1 (S), Q14.1 (S), Q15.1 (S), Q16.1 (S), Q17.1 (S), Q18.1 (S), Q19.1 (S), Q20.9 (EMITTER_1), Q20.11 (EMITTER_2), Q20.13 (EMITTER_3), Q20.15 (EMITTER_4), Q21.1 (S), Q22.1 (S), Q23.1 (S), Q24.1 (S), Q25.9 (EMITTER_1), Q25.11 (EMITTER_2), Q25.13 (EMITTER_3), Q25.15 (EMITTER_4), Q26.1 (S), Q27.1 (S), Q28.1 (S), Q29.1 (S), Q30.1 (S), Q31.1 (S), Q34.1 (S), Q36.1 (S), Q38.1 (S), Q40.1 (S), Q42.1 (S), Q43.1 (S), Q46.1 (S), Q48.1 (S), Q50.1 (S), Q52.1 (S), Q54.9 (EMITTER_1), Q54.11 (EMITTER_2), Q54.13 (EMITTER_3), Q54.15 (EMITTER_4), Q56.1 (S), Q58.9 (EMITTER_1), Q58.11 (EMITTER_2), Q58.13 (EMITTER_3), Q58.15 (EMITTER_4), Q59.9 (EMITTER_1), Q59.11 (EMITTER_2), Q59.13 (EMITTER_3), Q59.15 (EMITTER_4), R2.2, R4.1, R5.2, R9.1, R10.1, R11.1, R12.1, R13.1, R14.1, R15.2, R22.2, R23.2, R24.2, R25.2, R26.1, R27.1, R28.1, R29.1, R30.1, R31.1, R32.1, R33.1, R34.1, R35.2, R39.1, R40.2, R47.2, R48.2, R49.2, R50.2, R55.2, R56.2, R57.2, R58.2, R63.2, R64.2, R65.2, R66.2, R71.2, R72.2, R73.2, R74.2, R79.2, R80.2, R85.2, R88.2, R91.2, R94.2, R97.2, R98.2, R103.2, R106.2, R109.2, R112.2, R118.2, RTCBattery1.2 (-), RV1.3, RV2.3, RV3.3, U1.15 (GND)
GenE-CS: J7.7, P4.8
GenFuelPressure: IO3.6, RV2.1
GenHL-CS: J8.7, P4.10
GenHR-CS: J9.7, P4.12
GreyV: P4.23, Q10.2 (G), R40.1
IO12: C16.1, D3.1 (K), IO1.2, R19.2
IO13: C20.1, D7.1 (K), IO1.3, R44.2
IO14: IO1.4, Q9.2, R38.2
IO15: C17.1, D4.1 (K), IO1.5, R20.2
IO16: C21.1, D9.1 (K), IO1.6, R45.2
IO17: IO1.7, Q3.2
IO18: C19.1, D6.1 (K), IO1.8, R21.2
IO19: C23.1, D10.1 (K), IO1.9, R46.2
IO21: IO2.1, Q39.2
IO22: IO2.2, Q37.2
IO23: C29.1, D11.1 (K), IO2.3, R51.2
IO24: C34.1, D17.1 (K), IO2.4, R60.2
IO25: IO2.5, Q33.2
IO26: C32.1, D15.1 (K), IO2.6, R54.2
IO28: IO2.8, Q35.2
IO29: C31.1, D14.1 (K), IO2.9, R53.2
IO31: C37.1, D20.1 (K), IO3.1, R67.2
IO32: IO3.2, Q53.2
IO33: IO3.3, Q57.2
IO35: IO3.5, Q45.2
IO38: IO3.8, Q41.2
IO41: C33.1, D16.1 (K), IO4.1, R59.2
IO42: IO4.2, Q44.2
IO43: IC8.2 (LX), IO4.3, RV4.2
IO44: C38.1, D21.1 (K), IO4.4, R68.2
IO45: IO4.5, Q47.2
IO46: IC8.7 (LY), IO4.6, RV5.2
IO47: C39.1, D22.1 (K), IO4.7, R69.2
IO48: IO4.8, Q49.2
IO110: IO1.10, Q11.2
IO111: C18.1, D8.1 (K), IO1.11, R18.2
IO112: C22.1, D12.1 (K), IO1.12, R43.2
IO211: IO2.11, Q32.2
IO212: C30.1, D13.1 (K), IO2.12, R52.2
IO311: C36.1, D19.1 (K), IO3.11, R62.2
IO410: C40.1, D23.1 (K), IO4.10, R70.2
IO411: IO4.11, Q51.2
IO412: C35.1, D18.1 (K), IO4.12, R61.2
KLED: P6.2, Q34.2 (G), R85.1
KitchenTTL: P7.5, Q20.14 (COLLECTOR_3), RN6.2
LCDPOWER: P4.34, Q56.2 (G), R118.1
MISO: IC1.4 (2Y), J7.5, J8.5, J9.5, P4.5
MOSI: IC1.7 (3A), J7.6, J8.6, J9.6, P4.6
unnamed: 5VOut1.1, C10.1, IC3.6 (FEEDBACK/FB), L1.2
unnamed: C1.1, IC2.2 (DELAY)
unnamed: C2.1, IC2.4 (FEEDBACK), R2.1, R3.2
unnamed: C7.1, IC3.3 (CBOOST/CB)
unnamed: C7.2, D1.1 (K), IC3.1 (SWITCH_OUTPUT), L1.1
unnamed: C8.1, IC2.5 (~SHUTDOWN/SOFT-START)
unnamed: C12.1, U1.1 (C1+)
unnamed: C12.2, U1.3 (C1-)
unnamed: C13.2, U1.6 (VS-)
unnamed: C14.1, U1.4 (C2+)
unnamed: C14.2, U1.5 (C2-)
unnamed: C15.1, U1.2 (VS+)
unnamed: C27.1, IC7.3 (CBOOST/CB)
unnamed: C27.2, D5.1 (K), IC7.1 (SWITCH_OUTPUT), L3.1
unnamed: D2.1, IC2.8 (OUTPUT), L2.1
unnamed: D3.2 (A), Q4.2 (G), R19.1, R23.1
unnamed: D4.2 (A), Q5.2 (G), R20.1, R24.1
unnamed: D6.2 (A), Q7.2 (G), R21.1, R25.1
unnamed: D7.2 (A), Q12.2 (G), R44.1, R48.1
unnamed: D8.2 (A), Q6.2 (G), R18.1, R22.1
unnamed: D9.2 (A), Q13.2 (G), R45.1, R49.1
unnamed: D10.2 (A), Q15.2 (G), R46.1, R50.1
unnamed: D11.2 (A), Q16.2 (G), R51.1, R55.1
unnamed: D12.2 (A), Q14.2 (G), R43.1, R47.1
unnamed: D13.2 (A), Q17.2 (G), R52.1, R56.1
unnamed: D14.2 (A), Q18.2 (G), R53.1, R57.1
unnamed: D15.2 (A), Q19.2 (G), R54.1, R58.1
unnamed: D16.2 (A), Q21.2 (G), R59.1, R63.1
unnamed: D17.2 (A), Q22.2 (G), R60.1, R64.1
unnamed: D18.2 (A), Q23.2 (G), R61.1, R65.1
unnamed: D19.2 (A), Q24.2 (G), R62.1, R66.1
unnamed: D20.2 (A), Q26.2 (G), R67.1, R71.1
unnamed: D21.2 (A), Q27.2 (G), R68.1, R72.1
unnamed: D22.2 (A), Q28.2 (G), R69.1, R73.1
unnamed: D23.2 (A), Q29.2 (G), R70.1, R74.1
unnamed: IC2.1 (ERROR_FLAG), R1.1
unnamed: IC3.5 (SYNC), R4.2
unnamed: IC5.3 (+INA), R8.1, R9.2
unnamed: IC5.5 (+INB), J5.1
unnamed: IC6.3 (+INA), J4.1
unnamed: IC6.5 (+INB), J6.1
unnamed: IC7.5 (SYNC), R14.2
unnamed: J4.2, RV1.2
unnamed: J5.2, RV2.2
unnamed: J6.2, RV3.2
unnamed: LPWater1.1, Q9.3, R36.1, Z2.1
unnamed: Main1.2, Q1.2
unnamed: Q1.1, R5.1
unnamed: Q2.3 (D), R17.2
unnamed: Q3.1, R16.2, R17.1, Z1.2
unnamed: Q4.3 (D), Q58.2 (CATHODE_1)
unnamed: Q5.3 (D), Q58.4 (CATHODE_2)
unnamed: Q8.3 (D), R37.2
unnamed: Q9.1, R36.2, R37.1, Z2.2
unnamed: Q10.3 (D), R42.2
unnamed: Q11.1, R41.2, R42.1, Z3.2
unnamed: Q12.3 (D), Q59.2 (CATHODE_1)
unnamed: Q13.3 (D), Q59.4 (CATHODE_2)
unnamed: Q14.3 (D), Q59.8 (CATHODE_4)
unnamed: Q15.3 (D), Q59.6 (CATHODE_3)
unnamed: Q16.3 (D), Q20.8 (CATHODE_4)
unnamed: Q17.3 (D), Q20.2 (CATHODE_1)
unnamed: Q18.3 (D), Q20.4 (CATHODE_2)
unnamed: Q19.3 (D), Q20.6 (CATHODE_3)
unnamed: Q20.1 (ANODE_1), RN5.4
unnamed: Q20.3 (ANODE_2), RN5.3
unnamed: Q20.5 (ANODE_3), RN5.2
unnamed: Q20.7 (ANODE_4), RN5.1
unnamed: Q21.3 (D), Q25.8 (CATHODE_4)
unnamed: Q22.3 (D), Q25.2 (CATHODE_1)
unnamed: Q23.3 (D), Q25.4 (CATHODE_2)
unnamed: Q24.3 (D), Q25.6 (CATHODE_3)
unnamed: Q25.1 (ANODE_1), RN7.4
unnamed: Q25.3 (ANODE_2), RN7.3
unnamed: Q25.5 (ANODE_3), RN7.2
unnamed: Q25.7 (ANODE_4), RN7.1
unnamed: Q26.3 (D), Q54.8 (CATHODE_4)
unnamed: Q27.3 (D), Q54.2 (CATHODE_1)
unnamed: Q28.3 (D), Q54.4 (CATHODE_2)
unnamed: Q29.3 (D), Q54.6 (CATHODE_3)
unnamed: Q30.3 (D), R82.2
unnamed: Q31.3 (D), R84.2
unnamed: Q32.1, R81.2, R82.1, Z4.2
unnamed: Q33.1, R83.2, R84.1, Z5.2
unnamed: Q34.3 (D), R87.2
unnamed: Q35.1, R86.2, R87.1, Z6.2
unnamed: Q36.3 (D), R90.2
unnamed: Q37.1, R89.2, R90.1, Z7.2
unnamed: Q38.3 (D), R93.2
unnamed: Q39.1, R92.2, R93.1, Z8.2
unnamed: Q40.3 (D), R96.2
unnamed: Q41.1, R95.2, R96.1, Z9.2
unnamed: Q42.3 (D), R100.2
unnamed: Q43.3 (D), R102.2
unnamed: Q44.1, R99.2, R100.1, Z10.2
unnamed: Q45.1, R101.2, R102.1, Z11.2
unnamed: Q46.3 (D), R105.2
unnamed: Q47.1, R104.2, R105.1, Z12.2
unnamed: Q48.3 (D), R108.2
unnamed: Q49.1, R107.2, R108.1, Z13.2
unnamed: Q50.3 (D), R111.2
unnamed: Q51.1, R110.2, R111.1, Z14.2
unnamed: Q52.3 (D), R114.2
unnamed: Q53.1, R113.2, R114.1, Z15.2
unnamed: Q54.1 (ANODE_1), RN9.4
unnamed: Q54.3 (ANODE_2), RN9.3
unnamed: Q54.5 (ANODE_3), RN9.2
unnamed: Q54.7 (ANODE_4), RN9.1
unnamed: Q56.3 (D), Q57.1, R119.2
unnamed: Q58.1 (ANODE_1), RN1.4
unnamed: Q58.3 (ANODE_2), RN1.3
unnamed: Q58.5 (ANODE_3), RN1.2
unnamed: Q7.3 (D), Q58.6 (CATHODE_3)
unnamed: Q58.7 (ANODE_4), RN1.1
unnamed: Q6.3 (D), Q58.8 (CATHODE_4)
unnamed: Q59.1 (ANODE_1), RN3.4
unnamed: Q59.3 (ANODE_2), RN3.3
unnamed: Q59.5 (ANODE_3), RN3.2
unnamed: Q59.7 (ANODE_4), RN3.1
RTankPOWER: P4.33, Q8.2 (G), R35.1
RX232: IO3.10, U1.13 (R1IN)
S1-2: P4.9, Q58.14 (COLLECTOR_3), RN2.2
S1-4: P4.7, Q58.16 (COLLECTOR_4), RN2.1
S3-4: P4.11, Q58.12 (COLLECTOR_2), RN2.3
S4-4: P4.13, Q58.10 (COLLECTOR_1), RN2.4
SCL: IC4.16 (SCL), IC8.6 (SY), P7.8, R6.2
SDA: IC4.15 (SDA), IC8.3 (SX), P7.7, R7.2
SO1: P5.6, Q42.2 (G), R97.1
SO2: P5.7, Q46.2 (G), R103.1
SO3: P5.8, Q48.2 (G), R106.1
SO4: P5.9, Q50.2 (G), R109.1
SO5: P5.10, Q52.2 (G), R112.1
SO6: P4.18, Q43.2 (G), R98.1
SPIn1: P4.22, Q25.10 (COLLECTOR_1), RN8.4
SPIn2: P4.24, Q54.16 (COLLECTOR_4), RN10.1
SPIn3: P4.26, Q54.14 (COLLECTOR_3), RN10.2
SPIn4: P4.28, Q54.12 (COLLECTOR_2), RN10.3
SPIn5: P4.30, Q54.10 (COLLECTOR_1), RN10.4
STV: P4.25, Q2.2 (G), R15.1
SpareTTL: P6.6, Q20.10 (COLLECTOR_1), RN6.4
TX232: IO3.7, U1.14 (T1OUT)
WLED: P6.3, Q36.2 (G), R88.1
WP: P4.29, Q38.2 (G), R91.1
WPS: P4.14, Q25.16 (COLLECTOR_4), RN8.1
WSS: P4.20, Q25.12 (COLLECTOR_2), RN8.3
WSiren: P6.4, Q30.2 (G), R79.1

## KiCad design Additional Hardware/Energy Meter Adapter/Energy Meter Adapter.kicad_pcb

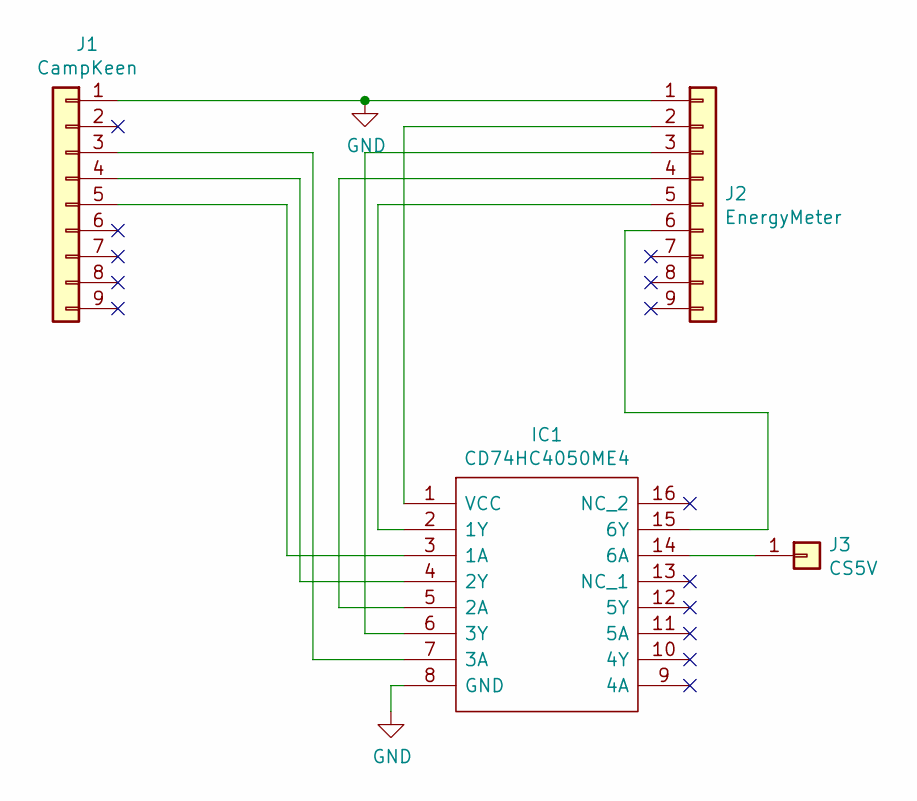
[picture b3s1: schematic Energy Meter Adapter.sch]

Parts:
IC1: CD74HC4050ME4; SOIC127P600X175-16N; Mouser Part Number 595-CD74HC4050ME4
J1: CampKeen; PinHeader_1x09_P2.54mm_Vertical
J2: EnergyMeter; PinSocket_1x09_P2.54mm_Vertical
J3: CS5V; PinSocket_1x01_P2.54mm_Vertical

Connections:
GND: IC1.8 (GND), J1.1, J2.1
unnamed: IC1.1 (VCC), J2.2
unnamed: IC1.2 (1Y), J2.5
unnamed: IC1.3 (1A), J1.5
unnamed: IC1.4 (2Y), J1.4
unnamed: IC1.5 (2A), J2.4
unnamed: IC1.6 (3Y), J2.3
unnamed: IC1.7 (3A), J1.3
unnamed: IC1.14 (6A), J3.1
unnamed: IC1.15 (6Y), J2.6

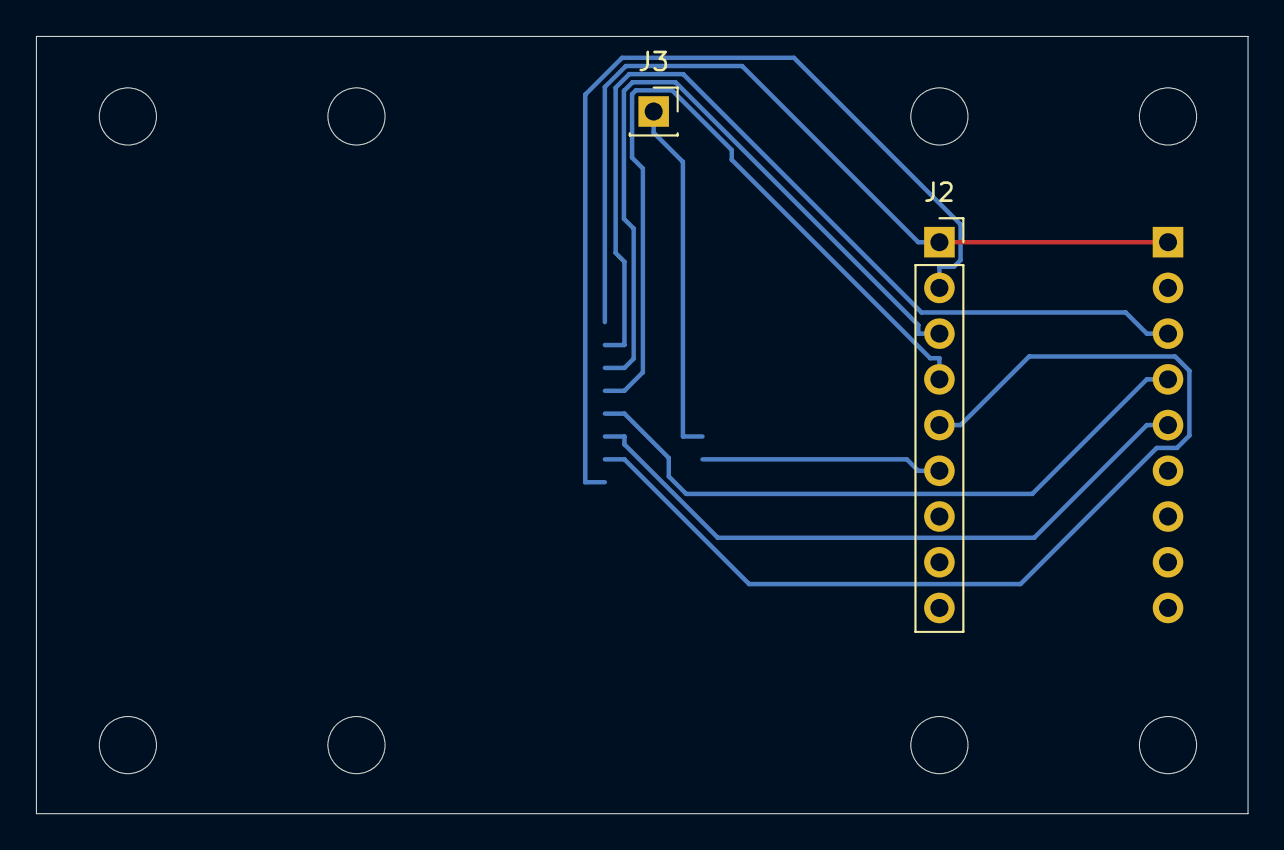
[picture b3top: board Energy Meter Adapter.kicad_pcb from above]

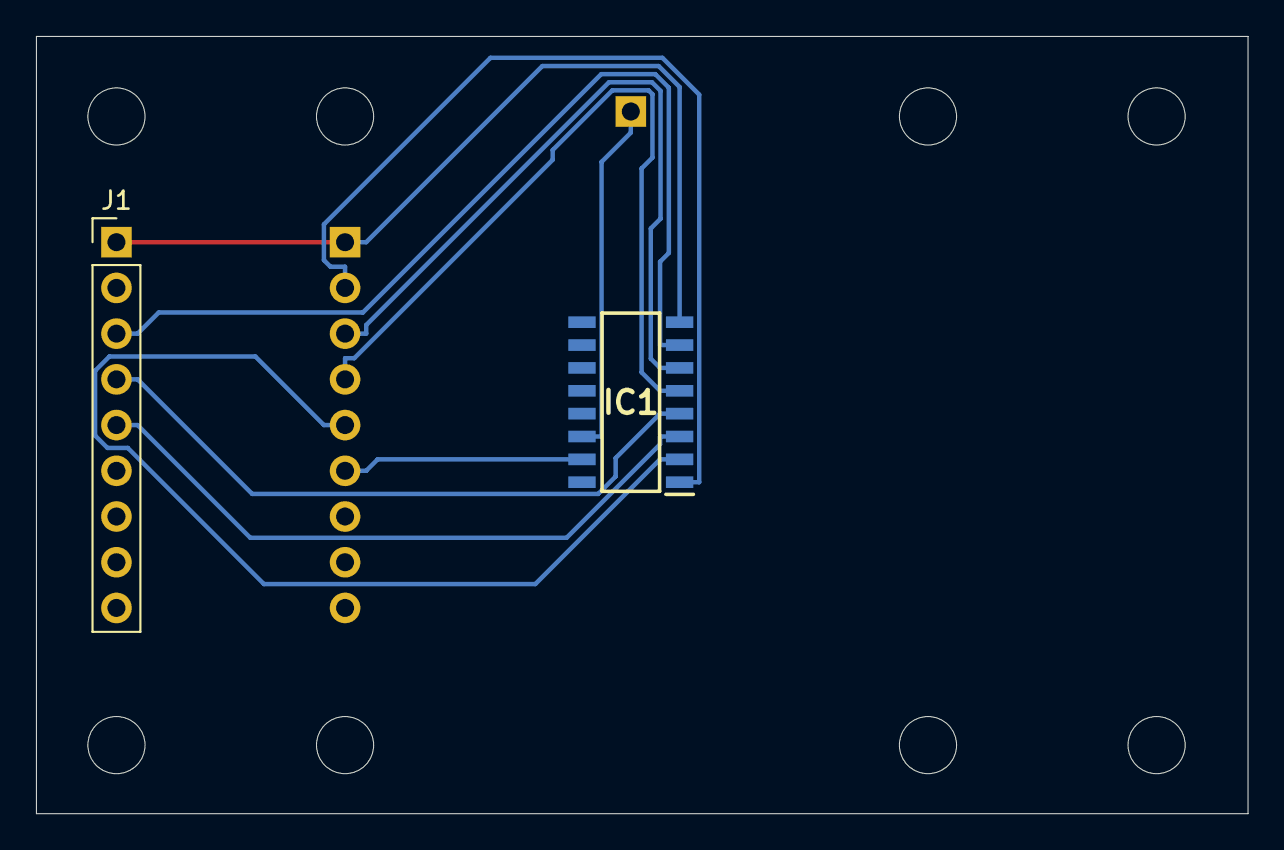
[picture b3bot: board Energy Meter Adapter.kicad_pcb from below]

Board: 2 copper layers, 67.3 x 43.2 mm, 4 parts (2 on the bottom side), 10 nets.
